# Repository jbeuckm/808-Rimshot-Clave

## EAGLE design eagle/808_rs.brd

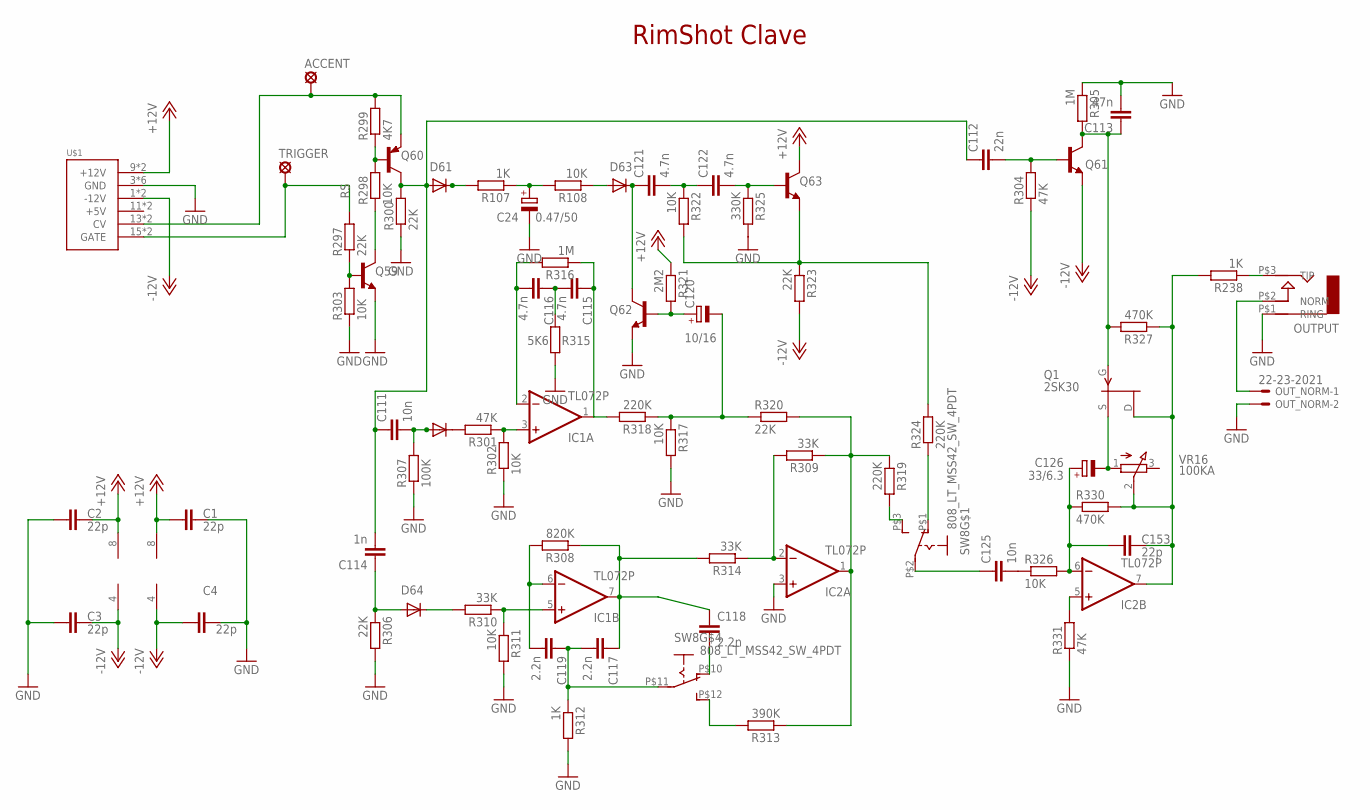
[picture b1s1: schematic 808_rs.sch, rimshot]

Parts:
ACCENT: LSP11
C1, C2, C3, C4: 22p; C050-024X044
C24: 0.47/50; E2,5-5
C111: 10n; C035-025X75
C112: 22n; C050-025X075
C113: 47n; C050-025X075
C114: 1n; C050-030X075
C115, C116: 4.7n; C035-025X75
C117, C119: 2.2n; C050-024X044
C118: 2.2n; C050-025X075
C120: 10/16; E2,5-6
C121: 4.7n; C050-025X075
C122: 4.7n; C050-030X075
C125: 10n; C050-025X075
C126: 33/6.3; E2,5-5
C153: 22p; C025-025X050
D61, D63, D64: 1N4148DO35-10; DO35-10
D62: 1N4148DO35-7; DO35-7
IC1, IC2: TL072P; DIL08
OUTPUT: AUDIO-JACK; ERTHENVAR-JACK-90DEG
OUT_NORM: 22-23-2021
Q1: 2SK30; TO92
Q59, Q61, Q62, Q63: 2N3904; TO92
Q60: 2N3906; TO92
R107, R312: 1K; 0207/5V
R108, R298, R302, R317: 10K; 0207/5V
R238: 1K; 0207/7
R297, R300, R323: 22K; 0207/5V
R299: 4K7; 0207/5V
R301, R304: 47K; 0207/5V
R303: 10K; 0207/2V
R305: 1M; 0207/5V
R306, R320: 22K; 0207/7
R307: 100K; 0207/5V
R308: 820K; 0207/5V
R309: 33K; 0207/2V
R310, R314: 33K; 0207/7
R311, R322: 10K; 0207/7
R313: 390K; 0207/7
R315: 5K6; 0207/5V
R316: 1M; 0207/2V
R318, R319: 220K; 0207/5V
R321: 2M2; 0207/7
R324: 220K; 0207/7
R325: 330K; 0207/7
R326: 10K; 0309/10
R327: 470K; 0207/5V
R330: 470K; 0207/2V
R331: 47K; 0207/7
SW8: 808_LT_MSS42_SW_4PDT; 808_LT_MSS42_SW_SLIDE
TRIGGER: LSP11
U$1: POWER; POWER_16
VR16: 100KA; 3RP/1610N

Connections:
+12V: C1.1, C2.2, IC1.8 (V+), IC2.8 (V+), Q63.1 (C), R321.1, U$1.9 (+12V), U$1.10 (+12V)
-12V: C3.2, C4.1, IC1.4 (V-), IC2.4 (V-), Q61.3 (E), R304.1, R323.2, U$1.1 (-12V), U$1.2 (-12V)
GND: C1.2, C2.1, C3.1, C4.2, C24.-, C113.2, IC2.3 (+IN), OUTPUT.P$1 (RING), OUT_NORM.2, Q59.3 (E), Q62.3 (E), R300.1, R302.1, R303.1, R305.1, R306.2, R307.1, R311.2, R312.2, R315.1, R317.2, R325.2, R331.1, U$1.3 (GND), U$1.4 (GND), U$1.5 (GND), U$1.6 (GND), U$1.7 (GND), U$1.8 (GND)
LT_LC_OUT: OUTPUT.P$3 (TIP), R238.1
unnamed: IC2.5 (+IN), R331.2
unnamed: C125.1, SW8.P$2
unnamed: IC2.2 (-IN), R309.2, R314.1
unnamed: C111.P$2 (2), D62.A, R307.2
unnamed: OUTPUT.P$2 (NORM), OUT_NORM.1
unnamed: R324.1, SW8.P$1 (O)
unnamed: R319.2, SW8.P$3 (S)
unnamed: C153.2, IC2.7 (OUT), Q1.1 (D), R238.2, R327.1, R330.2, VR16.2 (S)
unnamed: C113.1, Q1.2 (G), Q61.1 (C), R305.2, R327.2
unnamed: C112.2, Q61.2 (B), R304.2
unnamed: C118.2, SW8.P$10 (O)
unnamed: C24.+, R107.1, R108.2
unnamed: C121.1, D63.C, Q62.1 (C)
unnamed: C114.1, D64.A, R306.1
unnamed: C120.+, Q62.2 (B), R321.2
unnamed: R313.2, SW8.P$12 (S)
unnamed: Q60.2 (B), R298.2, R299.1
unnamed: Q59.2 (B), R297.1, R303.2
unnamed: Q59.1 (C), R298.1
unnamed: D61.C, R107.2
unnamed: D63.A, R108.1
unnamed: C121.2, C122.1, R322.1
unnamed: C122.2, Q63.2 (B), R325.1
unnamed: Q63.3 (E), R322.2, R323.1, R324.2
unnamed: D62.C, R301.2
unnamed: IC1.3 (+IN), R301.1, R302.2
unnamed: D64.C, R310.2
unnamed: IC1.5 (+IN), R310.1, R311.1
unnamed: C117.2, C119.1, R312.1, SW8.P$11
unnamed: C119.2, IC1.6 (-IN), R308.2
unnamed: C117.1, C118.1, IC1.7 (OUT), R308.1, R314.2
unnamed: IC2.1 (OUT), R309.1, R313.1, R319.1, R320.2
unnamed: C125.2, R326.1
unnamed: C126.+, C153.1, IC2.6 (-IN), R326.2, R330.1
unnamed: C126.-, Q1.3 (S), VR16.1 (A)
unnamed: C115.P$2 (2), C116.P$1 (1), R315.2
unnamed: C116.P$2 (2), IC1.2 (-IN), R316.2
unnamed: C115.P$1 (1), IC1.1 (OUT), R316.1, R318.2
unnamed: C120.-, R317.1, R318.1, R320.1
unnamed: C111.P$1 (1), C112.1, C114.2, D61.A, Q60.1 (C), R300.2
RS: R297.2, TRIGGER.MP, U$1.15 (GATE), U$1.16 (GATE)
TRIG: ACCENT.MP, Q60.3 (E), R299.2, U$1.13 (CV), U$1.14 (CV)

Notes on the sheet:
RimShot Clave

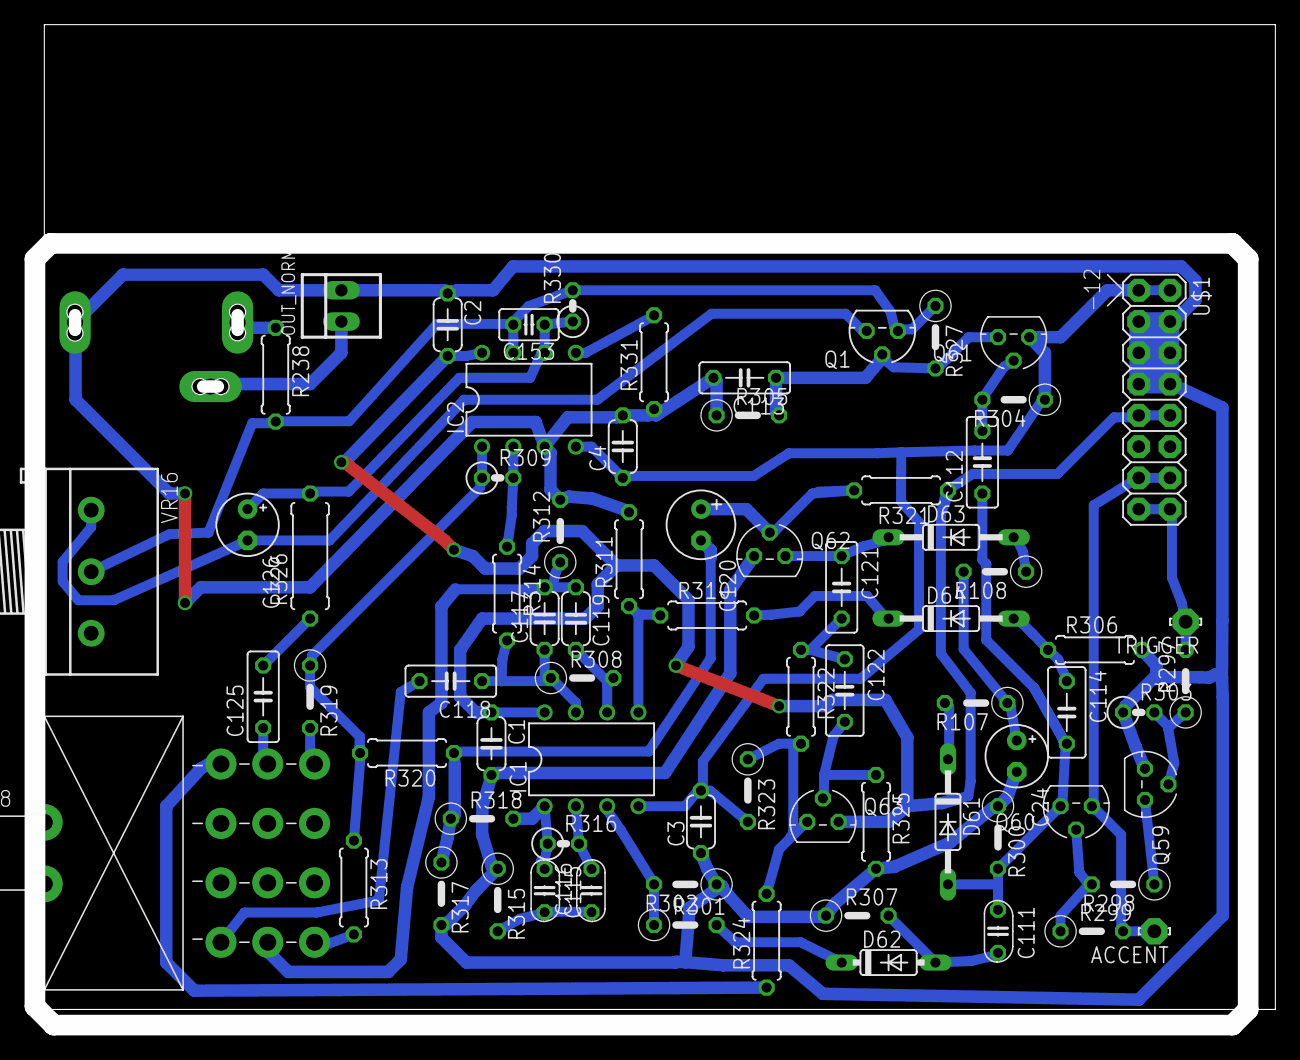
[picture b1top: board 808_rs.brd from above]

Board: 2 copper layers, 99.9 x 80.4 mm, 75 parts (0 on the bottom side), 46 nets.

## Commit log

2015-01-19 initla commit
2015-01-19 gcode with well separated traces
2016-05-02 schematic updated
2016-05-02 2sk30
2016-05-02 more placement
2016-05-02 restarted layout with care
2016-05-03 placed parts manually
2016-05-03 working up to route
2016-05-03 ar 90pct
2016-05-03 93pct auto
2016-05-03 95pct auto
2016-05-03 94pct auto
2016-05-04 routed
2016-05-04 almost rerouted
2016-05-04 rerouted
2016-05-04 tweaks
2016-05-04 project file
2016-05-10 gcode
2016-05-16 svg panel
